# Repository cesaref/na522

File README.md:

This is part of an experiment to see what claude can achieve with simple prompts. As of now, the boards and designs have not been checked
and validated, so do not trust the generated boards!

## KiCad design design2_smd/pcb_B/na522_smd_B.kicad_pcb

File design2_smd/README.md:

# Design 2: surface-mount "modern equivalent"

A plug-in replacement for the NA522 MM card in the NAC82.

- **Topology:** the same Naim discrete topology, so the gain, input loading and output behaviour match the original.
- **Parts:** precision components throughout.
- **Changes from the original** are all simulated; see `simulation/RESULTS.md`.
- **Boards:** a stereo pair is one **T** and one **B** board (mirror images).

## What changed from the original, and why

| Change | Original | Design 2 | Reason / effect (simulated) |
|---|---|---|---|
| RIAA network | R17 4K7, R21 82K, C5 47 µF | R17 4K7, **R21 63.4 k**, **C5 220 µF** | RIAA error 0.57 dB → **0.04 dB** (20 Hz–20 kHz). Values found by SPICE-in-the-loop search (`tools/optimise_riaa.py`); insensitive to hFE (0.75–1.4×) |
| Resistors | 1 % metal film (R12 1 %/50 ppm) | **0.1 %, 25 ppm thin film** (Vishay TNPW0805) | Monte Carlo RIAA spread (95th pct) 0.73 → 0.16 dB; channel match |
| RIAA capacitors | Polyester/film | **C0G/NP0 MLCC** (alt. PPS film) | Negligible voltage coefficient and dielectric absorption |
| Stage-1 feedback | R6 1K, R10 2K2, C3 47 µF | **R6 499 Ω, R10 1.1 k, C3 220 µF** | Same gain (×3.2); about half the feedback-network thermal noise. EIN 5.9 → 5.3 nV/√Hz |
| Input coupling C1 | 10 µF tantalum | **1 µF C0G** | No tantalum in the signal path. 0.96 Hz corner with the 165 k bias network |
| Bias divider | R3 330k direct from VCC | **R3 165k + R26 165k + C10 10 µF** (R1 62k → 75k keeps Zin 44 k) | Removes supply ripple from the input transistor base |
| Supply filter | R25 27 Ω, C8 47 µF | **R25 68 Ω, C8 470 µF**, plus C9 100 nF | 5 Hz corner. PSRR @100 Hz improves from −19.5 dB to **−46 dB** |
| Output coupling C7 | 10 µF tantalum | **47 µF electrolytic** | Less AC voltage across the electrolytic; no tantalum |
| Followers / sinks (Q3, Q5, Q8, Q10) | ZTX (E-line) | **BCX56-16, SOT-89** | ~0.1 W each: needs a SOT-89 package, not SOT-23 |
| Small-signal transistors | ZTX384C / ZTX214C | **BC850C / BC860C** (SOT-23) | Low-noise C-group parts |

Gain, input impedance (44 kΩ, 470 pF), output DC conditions, supply current (20 mA) and overload margin are essentially unchanged.

## Contents

Same structure as Design 1: `schematic/`, `bom/`, `simulation/`, `pcb_T/`, `pcb_B/`. See `../design1_tht/README.md` for the file-by-file table and the regeneration commands (replace `tht` with `smd`).

## Fabrication and assembly notes

- **Board:** 2 layers, FR-4 1.6 mm, 1 oz, **ENIG**. Same outline, holes, rules and DRC status as Design 1, with clearance ≥0.25 mm.
- **Components:** all SMD parts are on the **top** side, and pick-and-place files are provided (`pcb_*/*_pos.csv`). The four sockets are through-hole and fitted from the bottom; hand-solder them after reflow.
- **Stencil:** the paste layer is included (`*-F_Paste.gtp`).
- **Smallest parts:** 0805 passives and SOT-23, so it can be hand-assembled.
- **C8 voltage margin:** C8 runs at 65 % of its 35 V rating. Use the 50 V version if one is available in a 10 × 10 mm can.

## Key simulated figures

| | Value |
|---|---|
| Gain @1 kHz | 32.2 dB |
| RIAA deviation | ±0.04 dB from 20 Hz to 20 kHz (−0.2 dB @10 Hz). MC 95th percentile: 0.16 dB |
| Input impedance | 44.2 kΩ (+470 pF) |
| SNR re 5 mV, A-wtd | 84 dB with the input shorted, 78 dB with a cartridge |
| THD @1 kHz | 0.0065 % at 5 mV, 0.053 % at 50 mV |
| Overload @1 kHz | 184 mV |
| PSRR @100 Hz | −46 dB |
| Supply current | 20.2 mA |
| Power-up | +21 V transient at OUT (as the original); settles in ~13 s |

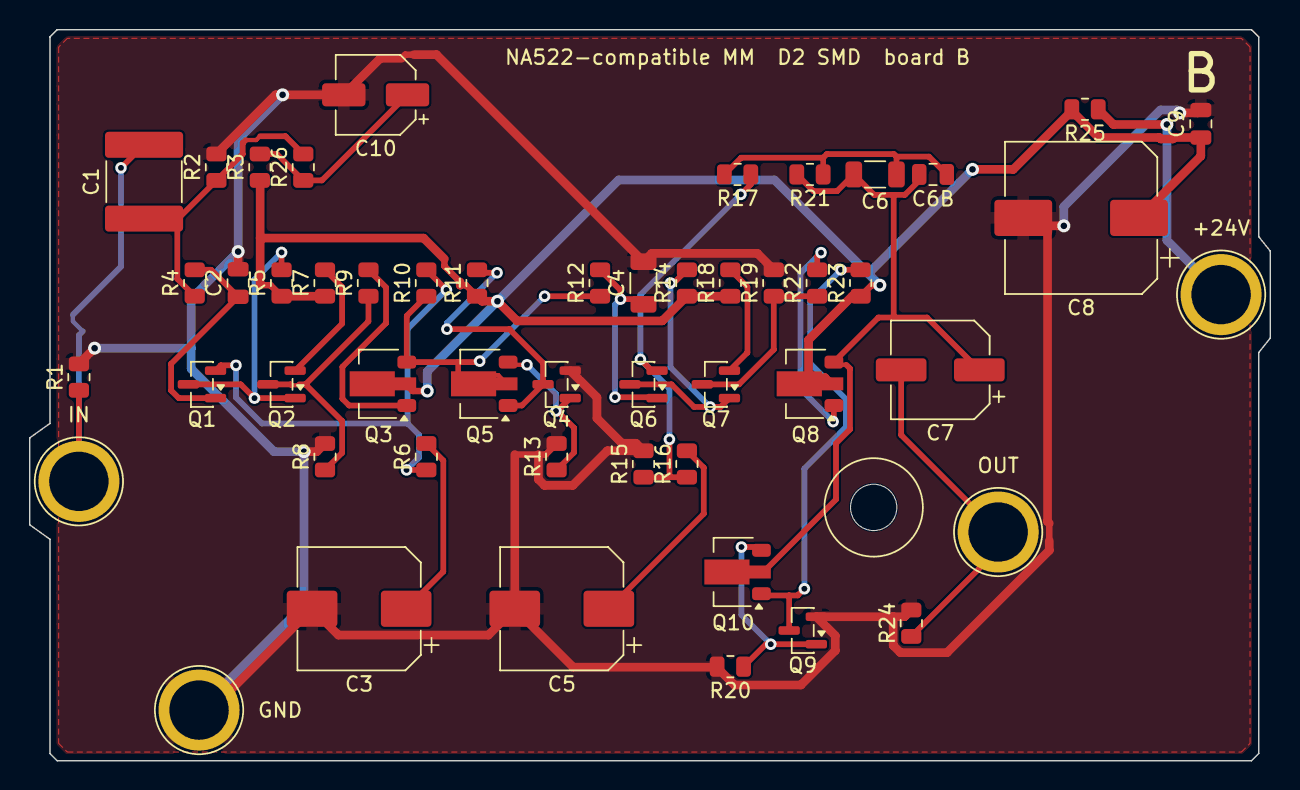
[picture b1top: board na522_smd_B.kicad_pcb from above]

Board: 2 copper layers, 85.7 x 50.5 mm, 52 parts (0 on the bottom side), 28 nets.

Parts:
C1: 1e+03nF; C_2220_5750Metric
C2: 470pF; C_0805_2012Metric
C3, C5: 220uF; CP_Elec_8x10
C4: 22nF; C_1206_3216Metric
C6: 68nF; C_1206_3216Metric
C6B: DNF; C_0805_2012Metric
C7: 47uF; CP_Elec_6.3x7.7
C8: 470uF; CP_Elec_10x10
C9: 100nF; C_0805_2012Metric
C10: 10uF; CP_Elec_5x5.8
H1: PEG; Peg_Hole_3.2mm
P1: Mill-Max 0391 (V24); Socket_MillMax_0391_Hole4.1mm
P2: Mill-Max 0391 (OUT); Socket_MillMax_0391_Hole4.1mm
P3: Mill-Max 0391 (GND); Socket_MillMax_0391_Hole4.1mm
P4: Mill-Max 0391 (IN); Socket_MillMax_0391_Hole4.1mm
Q1, Q4, Q6, Q9: BC850C; SOT-23
Q2, Q7: BC860C; SOT-23
Q3, Q5, Q8, Q10: BCX56-16; SOT-89-3
R1: 75k; R_0805_2012Metric
R2: 330k; R_0805_2012Metric
R3, R26: 165k; R_0805_2012Metric
R4: 470; R_0805_2012Metric
R5, R8, R14, R19: 22k; R_0805_2012Metric
R6: 499; R_0805_2012Metric
R7, R9, R18, R22: 1k; R_0805_2012Metric
R10: 1.1k; R_0805_2012Metric
R11, R23: 62k; R_0805_2012Metric
R12: 3.4k; R_0805_2012Metric
R13, R20, R25: 68; R_0805_2012Metric
R15: 220k; R_0805_2012Metric
R16: 390; R_0805_2012Metric
R17: 4.7k; R_0805_2012Metric
R21: 63.4k; R_0805_2012Metric
R24: 100k; R_0805_2012Metric

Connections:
B1: C1.1, R2.1, R4.1, R26.2
B1A: C2.1, Q1.1, R4.2
B1F: C10.1, R3.2, R26.1
B3: Q3.1, R9.2
B6: C4.1, Q6.1, R12.2
B8: Q8.1, R22.2
C3P: C3.1, R6.2
C5P: C5.1, R16.2
E1: Q1.2, R6.1, R10.2
E2: Q2.2, R7.2
E6: Q6.2, R15.1, R16.1, R17.1
E7: Q7.2, R18.2
F2: C6.1, C6B.1, R17.2, R21.1
GND: C2.2, C3.2, C4.2, C5.2, C8.2, C9.2, C10.2, P3.1, Q4.2, Q9.2, R1.2, R2.2, R8.2, R13.2, R15.2, R19.2, R20.2, R24.2
IN: C1.2, P4.1, R1.1
N1: Q1.3, Q2.1, R5.2
N2: Q2.3, R8.1, R9.1
N6: Q6.3, Q7.1, R14.2
N7: Q7.3, R19.1, R22.1
O1: Q3.3, Q5.2, R10.1, R12.1
O2: C6.2, C6B.2, C7.1, Q8.3, Q10.2, R21.2
OUT: C7.2, P2.1, R24.1
V24: P1.1, R25.1
VCC: C8.1, C9.1, Q3.2, Q8.2, R3.1, R5.1, R7.1, R11.1, R14.1, R18.1, R23.1, R25.2
Y1: Q4.3, Q5.1, R11.2
Y2: Q9.3, Q10.1, R23.2
Z1: Q4.1, Q5.3, R13.1
Z2: Q9.1, Q10.3, R20.1

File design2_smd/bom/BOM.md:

# Bill of materials - Design 2 - surface-mount (modern, RIAA-exact)

Quantities are per board; a stereo pair is one **T** and one **B** board (same BOM).
Generated by `tools/make_bom.py` from `tools/circuit.py`; DC voltages are from the simulated operating point.

| Ref | Value | Fit | Description | Manufacturer | MPN | DC check | Notes |
|---|---|---|---|---|---|---|---|
| R1 | 75k | fit | Thin film 0805, 0.125 W, 0.1 %, 25 ppm/K | Vishay | TNPW080575K0BEEA |  |  |
| C1 | 1uF | fit | MLCC C0G/NP0 1 uF 50 V 5 %, 2220 | TDK | C5750C0G1H105J230KA | Vdc=11.3 V (rated 50 V, 23 %) | Non-polar. 0.96 Hz with the 165k bias network. Alt: PPS/PEN film SMD 1 uF >= 25 V. |
| R3 | 165k | fit | Thin film 0805, 0.125 W, 0.1 %, 25 ppm/K | Vishay | TNPW0805165KBEEA |  |  |
| R26 | 165k | fit | Thin film 0805, 0.125 W, 0.1 %, 25 ppm/K | Vishay | TNPW0805165KBEEA |  |  |
| C10 | 10uF | fit | Al. electrolytic SMD 10 uF 50 V, 5x5.8 | Panasonic | EEE-FK1H100P | Vdc=11.3 V (rated 50 V, 23 %) | Bias-supply filter. |
| R2 | 330k | fit | Thin film 0805, 0.125 W, 0.1 %, 25 ppm/K | Vishay | TNPW0805330KBEEA |  |  |
| R4 | 470 | fit | Thin film 0805, 0.125 W, 0.1 %, 25 ppm/K | Vishay | TNPW0805470RBEEA |  |  |
| C2 | 470pF | fit | MLCC C0G 470 pF 50 V 5 %, 0805 | Murata | GRM2165C1H471JA01D | Vdc=11.3 V (rated 50 V, 23 %) | Cartridge load ~470 pF (as original). |
| Q1 | BC850C,215 | fit | NPN low-noise BC850C, SOT-23 (1=B 2=E 3=C) | Nexperia | BC850C,215 |  | OP: Ic=0.06 mA, Vce=10.7 V, Pd=1 mW. |
| R5 | 22k | fit | Thin film 0805, 0.125 W, 0.1 %, 25 ppm/K | Vishay | TNPW080522K0BEEA |  |  |
| Q2 | BC860C,215 | fit | PNP low-noise BC860C, SOT-23 (1=B 2=E 3=C) | Nexperia | BC860C,215 |  | OP: Ic=0.57 mA, Vce=10.7 V, Pd=6 mW. |
| R7 | 1k | fit | Thin film 0805, 0.125 W, 0.1 %, 25 ppm/K | Vishay | TNPW08051K00BEEA |  |  |
| R8 | 22k | fit | Thin film 0805, 0.125 W, 0.1 %, 25 ppm/K | Vishay | TNPW080522K0BEEA |  |  |
| R9 | 1k | fit | Thin film 0805, 0.125 W, 0.1 %, 25 ppm/K | Vishay | TNPW08051K00BEEA |  |  |
| Q3 | BCX56-16,115 | fit | NPN medium power BCX56-16, SOT-89 (1=B 2=C 3=E) | Nexperia | BCX56-16,115 |  | Followers / current sinks, ~9.2 mA, ~0.13 W each. OP: Ic=9.10 mA, Vce=12.0 V, Pd=109 mW. |
| R10 | 1.1k | fit | Thin film 0805, 0.125 W, 0.1 %, 25 ppm/K | Vishay | TNPW08051K10BEEA |  |  |
| R6 | 499 | fit | Thin film 0805, 0.125 W, 0.1 %, 25 ppm/K | Vishay | TNPW0805499RBEEA |  |  |
| C3 | 220uF | fit | Al. electrolytic SMD 220 uF 35 V, 8x10.2 | Panasonic | EEE-FK1V221P | Vdc=10.7 V (rated 35 V, 31 %) | Stage-1 feedback leg. |
| Q5 | BCX56-16,115 | fit | NPN medium power BCX56-16, SOT-89 (1=B 2=C 3=E) | Nexperia | BCX56-16,115 |  | Followers / current sinks, ~9.2 mA, ~0.13 W each. OP: Ic=9.21 mA, Vce=10.0 V, Pd=92 mW. |
| R11 | 62k | fit | Thin film 0805, 0.125 W, 0.1 %, 25 ppm/K | Vishay | TNPW080562K0BEEA |  |  |
| Q4 | BC850C,215 | fit | NPN low-noise BC850C, SOT-23 (1=B 2=E 3=C) | Nexperia | BC850C,215 |  | OP: Ic=0.29 mA, Vce=1.3 V, Pd=0 mW. |
| R13 | 68 | fit | Thin film 0805, 0.125 W, 0.1 %, 25 ppm/K | Vishay | TNPW080568R0BEEA |  |  |
| R12 | 3.4k | fit | Thin film 0805, 0.125 W, 0.1 %, 25 ppm/K | Vishay | TNPW08053K40BEEA |  | RIAA 75 us - 1 %/50 ppm minimum (original spec) |
| C4 | 22nF | fit | MLCC C0G 22 nF 50 V 5 %, 1206 | Murata | GRM3195C1H223JA01D | Vdc=10.7 V (rated 50 V, 21 %) | RIAA 75 us. Alt: Panasonic ECHU (PPS film) 22 nF 2 %. |
| Q6 | BC850C,215 | fit | NPN low-noise BC850C, SOT-23 (1=B 2=E 3=C) | Nexperia | BC850C,215 |  | OP: Ic=0.05 mA, Vce=11.4 V, Pd=1 mW. |
| R14 | 22k | fit | Thin film 0805, 0.125 W, 0.1 %, 25 ppm/K | Vishay | TNPW080522K0BEEA |  |  |
| Q7 | BC860C,215 | fit | PNP low-noise BC860C, SOT-23 (1=B 2=E 3=C) | Nexperia | BC860C,215 |  | OP: Ic=0.52 mA, Vce=11.9 V, Pd=6 mW. |
| R18 | 1k | fit | Thin film 0805, 0.125 W, 0.1 %, 25 ppm/K | Vishay | TNPW08051K00BEEA |  |  |
| R19 | 22k | fit | Thin film 0805, 0.125 W, 0.1 %, 25 ppm/K | Vishay | TNPW080522K0BEEA |  |  |
| R22 | 1k | fit | Thin film 0805, 0.125 W, 0.1 %, 25 ppm/K | Vishay | TNPW08051K00BEEA |  |  |
| Q8 | BCX56-16,115 | fit | NPN medium power BCX56-16, SOT-89 (1=B 2=C 3=E) | Nexperia | BCX56-16,115 |  | Followers / current sinks, ~9.2 mA, ~0.13 W each. OP: Ic=9.15 mA, Vce=13.1 V, Pd=120 mW. |
| R15 | 220k | fit | Thin film 0805, 0.125 W, 0.1 %, 25 ppm/K | Vishay | TNPW0805220KBEEA |  |  |
| R16 | 390 | fit | Thin film 0805, 0.125 W, 0.1 %, 25 ppm/K | Vishay | TNPW0805390RBEEA |  | RIAA network |
| C5 | 220uF | fit | Al. electrolytic SMD 220 uF 35 V, 8x10.2 | Panasonic | EEE-FK1V221P | Vdc=10.1 V (rated 35 V, 29 %) | Stage-2 RIAA feedback leg. |
| R17 | 4.7k | fit | Thin film 0805, 0.125 W, 0.1 %, 25 ppm/K | Vishay | TNPW08054K70BEEA |  | RIAA network |
| R21 | 63.4k | fit | Thin film 0805, 0.125 W, 0.1 %, 25 ppm/K | Vishay | TNPW080563K4BEEA |  | RIAA network |
| C6 | 68nF | fit | MLCC C0G 68 nF 50 V 5 %, 1206 | TDK | C3216C0G1H683J160AA | Vdc=0.5 V (rated 50 V, 1 %) | RIAA 3180/318 us. Alt: Panasonic ECHU (PPS film) 68 nF 2 %. |
| C6B | 1nF | DNF | MLCC C0G 1 nF 50 V 5 %, 0805 | Murata | GRM2165C1H102JA01D | Vdc=0.5 V (rated 50 V, 1 %) | NOT FITTED (RIAA trim position). |
| Q10 | BCX56-16,115 | fit | NPN medium power BCX56-16, SOT-89 (1=B 2=C 3=E) | Nexperia | BCX56-16,115 |  | Followers / current sinks, ~9.2 mA, ~0.13 W each. OP: Ic=9.20 mA, Vce=8.9 V, Pd=82 mW. |
| R23 | 62k | fit | Thin film 0805, 0.125 W, 0.1 %, 25 ppm/K | Vishay | TNPW080562K0BEEA |  |  |
| Q9 | BC850C,215 | fit | NPN low-noise BC850C, SOT-23 (1=B 2=E 3=C) | Nexperia | BC850C,215 |  | OP: Ic=0.29 mA, Vce=1.3 V, Pd=0 mW. |
| R20 | 68 | fit | Thin film 0805, 0.125 W, 0.1 %, 25 ppm/K | Vishay | TNPW080568R0BEEA |  |  |
| C7 | 47uF | fit | Al. electrolytic SMD 47 uF 35 V, 6.3x7.7 | Panasonic | EEE-FK1V470P | Vdc=9.6 V (rated 35 V, 27 %) | Output coupling; + to O2. |
| R24 | 100k | fit | Thin film 0805, 0.125 W, 0.1 %, 25 ppm/K | Vishay | TNPW0805100KBEEA |  |  |
| R25 | 68 | fit | Thin film 0805, 0.125 W, 0.1 %, 25 ppm/K | Vishay | TNPW080568R0BEEA |  |  |
| C8 | 470uF | fit | Al. electrolytic SMD 470 uF 35 V, 10x10.2 | Panasonic | EEE-FK1V471P | Vdc=22.6 V (rated 35 V, 65 %) | Supply reservoir (5 Hz filter with R25). |
| C9 | 100nF | fit | MLCC X7R 100 nF 50 V, 0805 | Murata | GRM21BR71H104KA01L | Vdc=22.6 V (rated 50 V, 45 %) | HF bypass. |
| P1 | socket | fit | Receptacle for 0.8 x 1.7 mm blade pin (1.65-2.08 mm #07 contact), gold | Mill-Max | 0391-0-15-15-07-27-10-0 |  | Fitted from the UNDERSIDE (through-hole, hand solder). Test-fit samples first. |
| P2 | socket | fit | Receptacle for 0.8 x 1.7 mm blade pin (1.65-2.08 mm #07 contact), gold | Mill-Max | 0391-0-15-15-07-27-10-0 |  | Fitted from the UNDERSIDE (through-hole, hand solder). Test-fit samples first. |
| P3 | socket | fit | Receptacle for 0.8 x 1.7 mm blade pin (1.65-2.08 mm #07 contact), gold | Mill-Max | 0391-0-15-15-07-27-10-0 |  | Fitted from the UNDERSIDE (through-hole, hand solder). Test-fit samples first. |
| P4 | socket | fit | Receptacle for 0.8 x 1.7 mm blade pin (1.65-2.08 mm #07 contact), gold | Mill-Max | 0391-0-15-15-07-27-10-0 |  | Fitted from the UNDERSIDE (through-hole, hand solder). Test-fit samples first. |

MPNs for passives are given as examples that meet the specification; check stock/ordering codes. Items marked *series* need the ordering code chosen for the stated value/voltage/pitch.

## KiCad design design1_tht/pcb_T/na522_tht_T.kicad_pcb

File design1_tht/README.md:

# Design 1: through-hole, faithful NA322/4 topology

A plug-in replacement for the Naim NA522 MM phono card in the NAC82.

- **Circuit:** the traced NA322/4 circuit with its original values.
- **Parts:** modern through-hole equivalents (see `bom/`).
- **Optional additions:** two positions for later improvements. Both are inactive in the default build:
  - R26/C10, a bias-supply filter. R26 is fitted as a 0 Ω link and C10 is not fitted.
  - C9, an HF bypass (not fitted).
- **Boards:** a stereo pair is one **T** and one **B** board. They are mirror images, as on the original cards.

Read `../DESIGN.md` first for the background, the reverse-engineering evidence and the open questions.

## Contents

| Path | What |
|---|---|
| `schematic/na522_tht_schematic.{pdf,svg,png}` | Schematic with values (drawn from `tools/circuit.py`) |
| `bom/BOM.md`, `bom/*.csv` | BOM per reference and grouped, with MPNs and capacitor DC-voltage/rating checks from the simulated operating point |
| `simulation/RESULTS.md` | Full ngspice characterisation: gain, RIAA error, Monte Carlo, noise, THD, overload, Zin/Zout, PSRR, power-up, DC operating point, temperature drift |
| `simulation/netlists/*.cir` | Every netlist simulated; re-run with `ngspice -b file.cir` inside that folder |
| `pcb_T/`, `pcb_B/` | KiCad 10 boards (`.kicad_pcb`), Gerbers (`gerbers/` + `_gerbers.zip`), Excellon drill + drill maps, pick-and-place `_pos.csv`, assembly PDF, renders, copper SVGs, DRC report |
| `../common/TEST_PROCEDURE.md` | Slot verification, assembly, bring-up voltages, AC acceptance tests |
| `../common/mechanical/` | Connector/peg coordinates, dimensioned drawings, annotated photographs |

## Fabrication notes (both T and B)

| Item | Value |
|---|---|
| Layers | 2, FR-4, 1.6 mm, 35 µm (1 oz) copper |
| Finish | ENIG preferred (gold to suit the gold socket contacts); HASL is acceptable |
| Outline | 83.5 × 50.5 mm, 0.5 mm corner chamfers, plus two small "ears" (≤1.4 mm) next to P1/P4. See `DESIGN.md` §6.3 |
| Tracks / clearance | All tracks 0.4 mm (supply current is 20 mA); clearance ≥0.3 mm; edge keep-out 1 mm |
| Vias | 0.8 mm pad, 0.4 mm drill |
| Holes | Sockets: 4.1 mm plated, 5.6 mm pad. Peg: 3.2 mm non-plated |
| Copper pours | GND on both layers |
| Solder mask / silk | Green / white; the bottom silk carries the "sockets on THIS side" note |
| DRC | 0 errors, 0 unconnected (KiCad 10.0.8). Warnings are silkscreen overlaps only, plus "library not found" because KiCad's global footprint table is not configured on the build machine |

Each `pcb_*/gerbers/` folder contains all of these:

- `*-F_Cu.gtl` and `*-B_Cu.gbl`
- `*-F_Mask.gts` and `*-B_Mask.gbs`
- `*-F_Silkscreen.gto` and `*-B_Silkscreen.gbo`
- `*-F_Paste.gtp` and `*-B_Paste.gbp`
- `*-Edge_Cuts.gm1`
- `*-PTH.drl` and `*-NPTH.drl`
- the drill map PDFs
- `*-job.gbrjob`

Upload `*_gerbers.zip` to the board house. **Order the T and B boards as two separate designs.**

## Key simulated figures (47 kΩ load, 24 V supply)

| | Value |
|---|---|
| Gain @1 kHz | 32.2 dB |
| RIAA deviation | +0.44 dB @20 Hz, +0.40 dB @50 Hz, ≤0.07 dB from 100 Hz to 20 kHz. MC 95th percentile: 0.73 dB |
| Input impedance | 44.7 kΩ (R1 62k ‖ R2/R3 165k), plus ~470 pF (C2 via R4) |
| SNR re 5 mV, A-wtd | 83 dB with the input shorted, 78 dB with a 1 k + 500 mH cartridge |
| THD @1 kHz | 0.0065 % at 5 mV in |
| Overload @1 kHz | 181 mV (31 dB margin) |
| PSRR @100 Hz | **−19.5 dB**. The original relies on a clean, regulated 24 V. Fit option R26/C10 + C9 to improve it (see `DESIGN.md` §5.4) |
| Supply current | 20.4 mA |

## Value options

- **'riaa'**: R21 = 73.2 k and R17 = 4.75 k (was 82 k / 4.7 k). The maximum RIAA error from 20 Hz to 20 kHz falls from 0.57 dB to 0.13 dB, a deliberate departure from the Naim voicing.
- **Bias filter**: R3 = 165 k, R26 = 165 k, C10 = 10 µF, and R1 = 75 k to keep Zin ≈ 45 k. This mirrors Design 2.

## Regenerating

From the repo root:

```
/opt/homebrew/bin/python3.14 tools/simulate.py tht          # simulation
work/venv/bin/python tools/draw_schematic.py                # schematic
/opt/homebrew/bin/python3.14 tools/make_bom.py              # BOM
$KPY tools/build_pcb.py tht T ; $KPY tools/build_pcb.py tht B   # place, autoroute, DRC, Gerbers
```

where `KPY=~/Applications/KiCad/KiCad.app/Contents/Frameworks/Python.framework/Versions/Current/bin/python3`.

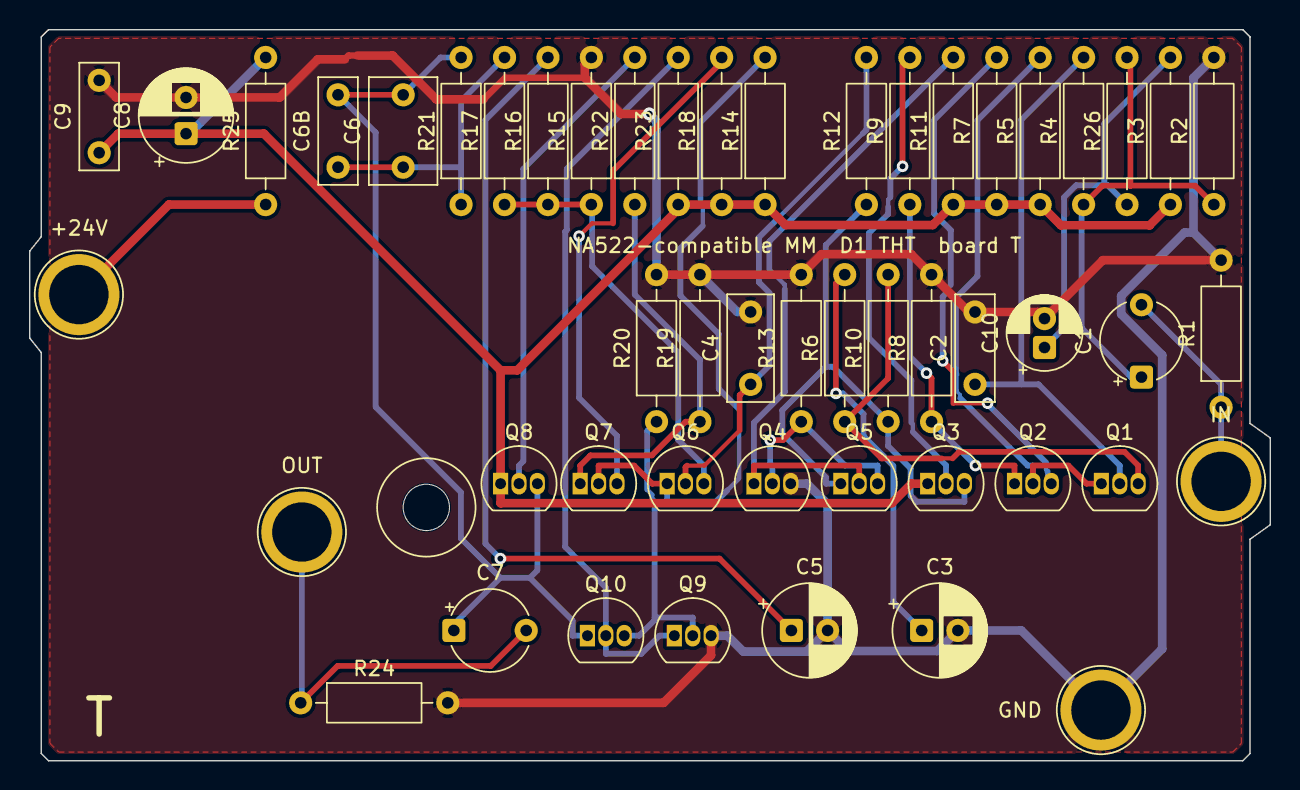
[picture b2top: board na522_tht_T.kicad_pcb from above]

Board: 2 copper layers, 85.7 x 50.5 mm, 52 parts (0 on the bottom side), 28 nets.

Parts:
C1, C7: 10uF; CP_Radial_Tantal_D5.5mm_P5.00mm
C2: 470pF; C_Rect_L7.2mm_W2.5mm_P5.00mm_FKS2_FKP2_MKS2_MKP2
C3, C5, C8: 47uF; CP_Radial_D6.3mm_P2.50mm
C4: 22nF; C_Rect_L7.2mm_W3.0mm_P5.00mm_FKS2_FKP2_MKS2_MKP2
C6: 68nF; C_Rect_L7.2mm_W4.5mm_P5.00mm_FKS2_FKP2_MKS2_MKP2
C6B, C9: DNF; C_Rect_L7.2mm_W2.5mm_P5.00mm_FKS2_FKP2_MKS2_MKP2
C10: DNF; CP_Radial_D5.0mm_P2.00mm
H1: PEG; Peg_Hole_3.2mm
P1: Mill-Max 0391 (V24); Socket_MillMax_0391_Hole4.1mm
P2: Mill-Max 0391 (OUT); Socket_MillMax_0391_Hole4.1mm
P3: Mill-Max 0391 (GND); Socket_MillMax_0391_Hole4.1mm
P4: Mill-Max 0391 (IN); Socket_MillMax_0391_Hole4.1mm
Q1, Q3, Q4, Q5, Q6, Q8, Q9, Q10: BC550C; TO-92_Inline
Q2, Q7: BC560C; TO-92_Inline
R1, R11, R23: 62k; R_Axial_DIN0207_L6.3mm_D2.5mm_P10.16mm_Horizontal
R2, R3: 330k; R_Axial_DIN0207_L6.3mm_D2.5mm_P10.16mm_Horizontal
R4: 470; R_Axial_DIN0207_L6.3mm_D2.5mm_P10.16mm_Horizontal
R5, R8, R14, R19: 22k; R_Axial_DIN0207_L6.3mm_D2.5mm_P10.16mm_Horizontal
R6, R7, R9, R18, R22: 1k; R_Axial_DIN0207_L6.3mm_D2.5mm_P10.16mm_Horizontal
R10: 2.2k; R_Axial_DIN0207_L6.3mm_D2.5mm_P10.16mm_Horizontal
R12: 3.4k; R_Axial_DIN0207_L6.3mm_D2.5mm_P10.16mm_Horizontal
R13, R20: 68; R_Axial_DIN0207_L6.3mm_D2.5mm_P10.16mm_Horizontal
R15: 220k; R_Axial_DIN0207_L6.3mm_D2.5mm_P10.16mm_Horizontal
R16: 390; R_Axial_DIN0207_L6.3mm_D2.5mm_P10.16mm_Horizontal
R17: 4.7k; R_Axial_DIN0207_L6.3mm_D2.5mm_P10.16mm_Horizontal
R21: 82k; R_Axial_DIN0207_L6.3mm_D2.5mm_P10.16mm_Horizontal
R24: 100k; R_Axial_DIN0207_L6.3mm_D2.5mm_P10.16mm_Horizontal
R25: 27; R_Axial_DIN0207_L6.3mm_D2.5mm_P10.16mm_Horizontal
R26: 0R link; R_Axial_DIN0207_L6.3mm_D2.5mm_P10.16mm_Horizontal

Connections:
B1: C1.1, R2.1, R4.1, R26.2
B1A: C2.1, Q1.2, R4.2
B1F: C10.1, R3.2, R26.1
B3: Q3.2, R9.2
B6: C4.1, Q6.2, R12.2
B8: Q8.2, R22.2
C3P: C3.1, R6.2
C5P: C5.1, R16.2
E1: Q1.3, R6.1, R10.2
E2: Q2.3, R7.2
E6: Q6.3, R15.1, R16.1, R17.1
E7: Q7.3, R18.2
F2: C6.1, C6B.1, R17.2, R21.1
GND: C2.2, C3.2, C4.2, C5.2, C8.2, C9.2, C10.2, P3.1, Q4.3, Q9.3, R1.2, R2.2, R8.2, R13.2, R15.2, R19.2, R20.2, R24.2
IN: C1.2, P4.1, R1.1
N1: Q1.1, Q2.2, R5.2
N2: Q2.1, R8.1, R9.1
N6: Q6.1, Q7.2, R14.2
N7: Q7.1, R19.1, R22.1
O1: Q3.3, Q5.1, R10.1, R12.1
O2: C6.2, C6B.2, C7.1, Q8.3, Q10.1, R21.2
OUT: C7.2, P2.1, R24.1
V24: P1.1, R25.1
VCC: C8.1, C9.1, Q3.1, Q8.1, R3.1, R5.1, R7.1, R11.1, R14.1, R18.1, R23.1, R25.2
Y1: Q4.1, Q5.2, R11.2
Y2: Q9.1, Q10.2, R23.2
Z1: Q4.2, Q5.3, R13.1
Z2: Q9.2, Q10.3, R20.1
